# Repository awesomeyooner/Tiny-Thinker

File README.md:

# Tiny-Thinker
Barebones STM32 board I made to learn PCB design. I took inspiration from [this tutorial](https://www.youtube.com/watch?v=aVUqaB0IMh4) as well as many other videos from PhilsLab, Robert Feranec, and many more!

## Resources

Instead of putting them here, I've put all my notes in this [repo!](https://github.com/awesomeyooner/KiCAD-Library/blob/main/docs/notes/Getting-Started.md)

I hope they're useful!

## Features

This is a 4-Layer PCB centered around the **STM32F446RCT6** (same as STM32F446RET6 but with less flash) with the following stackup:

- **L1** - SIGNAL (with GND Pour)
- **L2** - GND Plane
- **L3** - GND Plane
- **L4** - 3.3V PWR Plane + SIGNAL

Implemented Features:
- USB C FS (Device only)
- 5V Power Multiplexing (5V from USB + 5V from external source)
- User-toggleable LED
- PWR LED
- 2 2x20 Header pins for stackable expansion boards

This board breaks out the following:
- SPI1 and SPI2 (with CS)
- I2C1
- CAN1 (No Transciever)
- SWDIO
- USB_FS
- 8 x TIM Channels
- 4 x ADC Channels
- 4 x GPIO

## Pictures

### Schematic

### Layout and Routing

### CAD

### Assembled Product

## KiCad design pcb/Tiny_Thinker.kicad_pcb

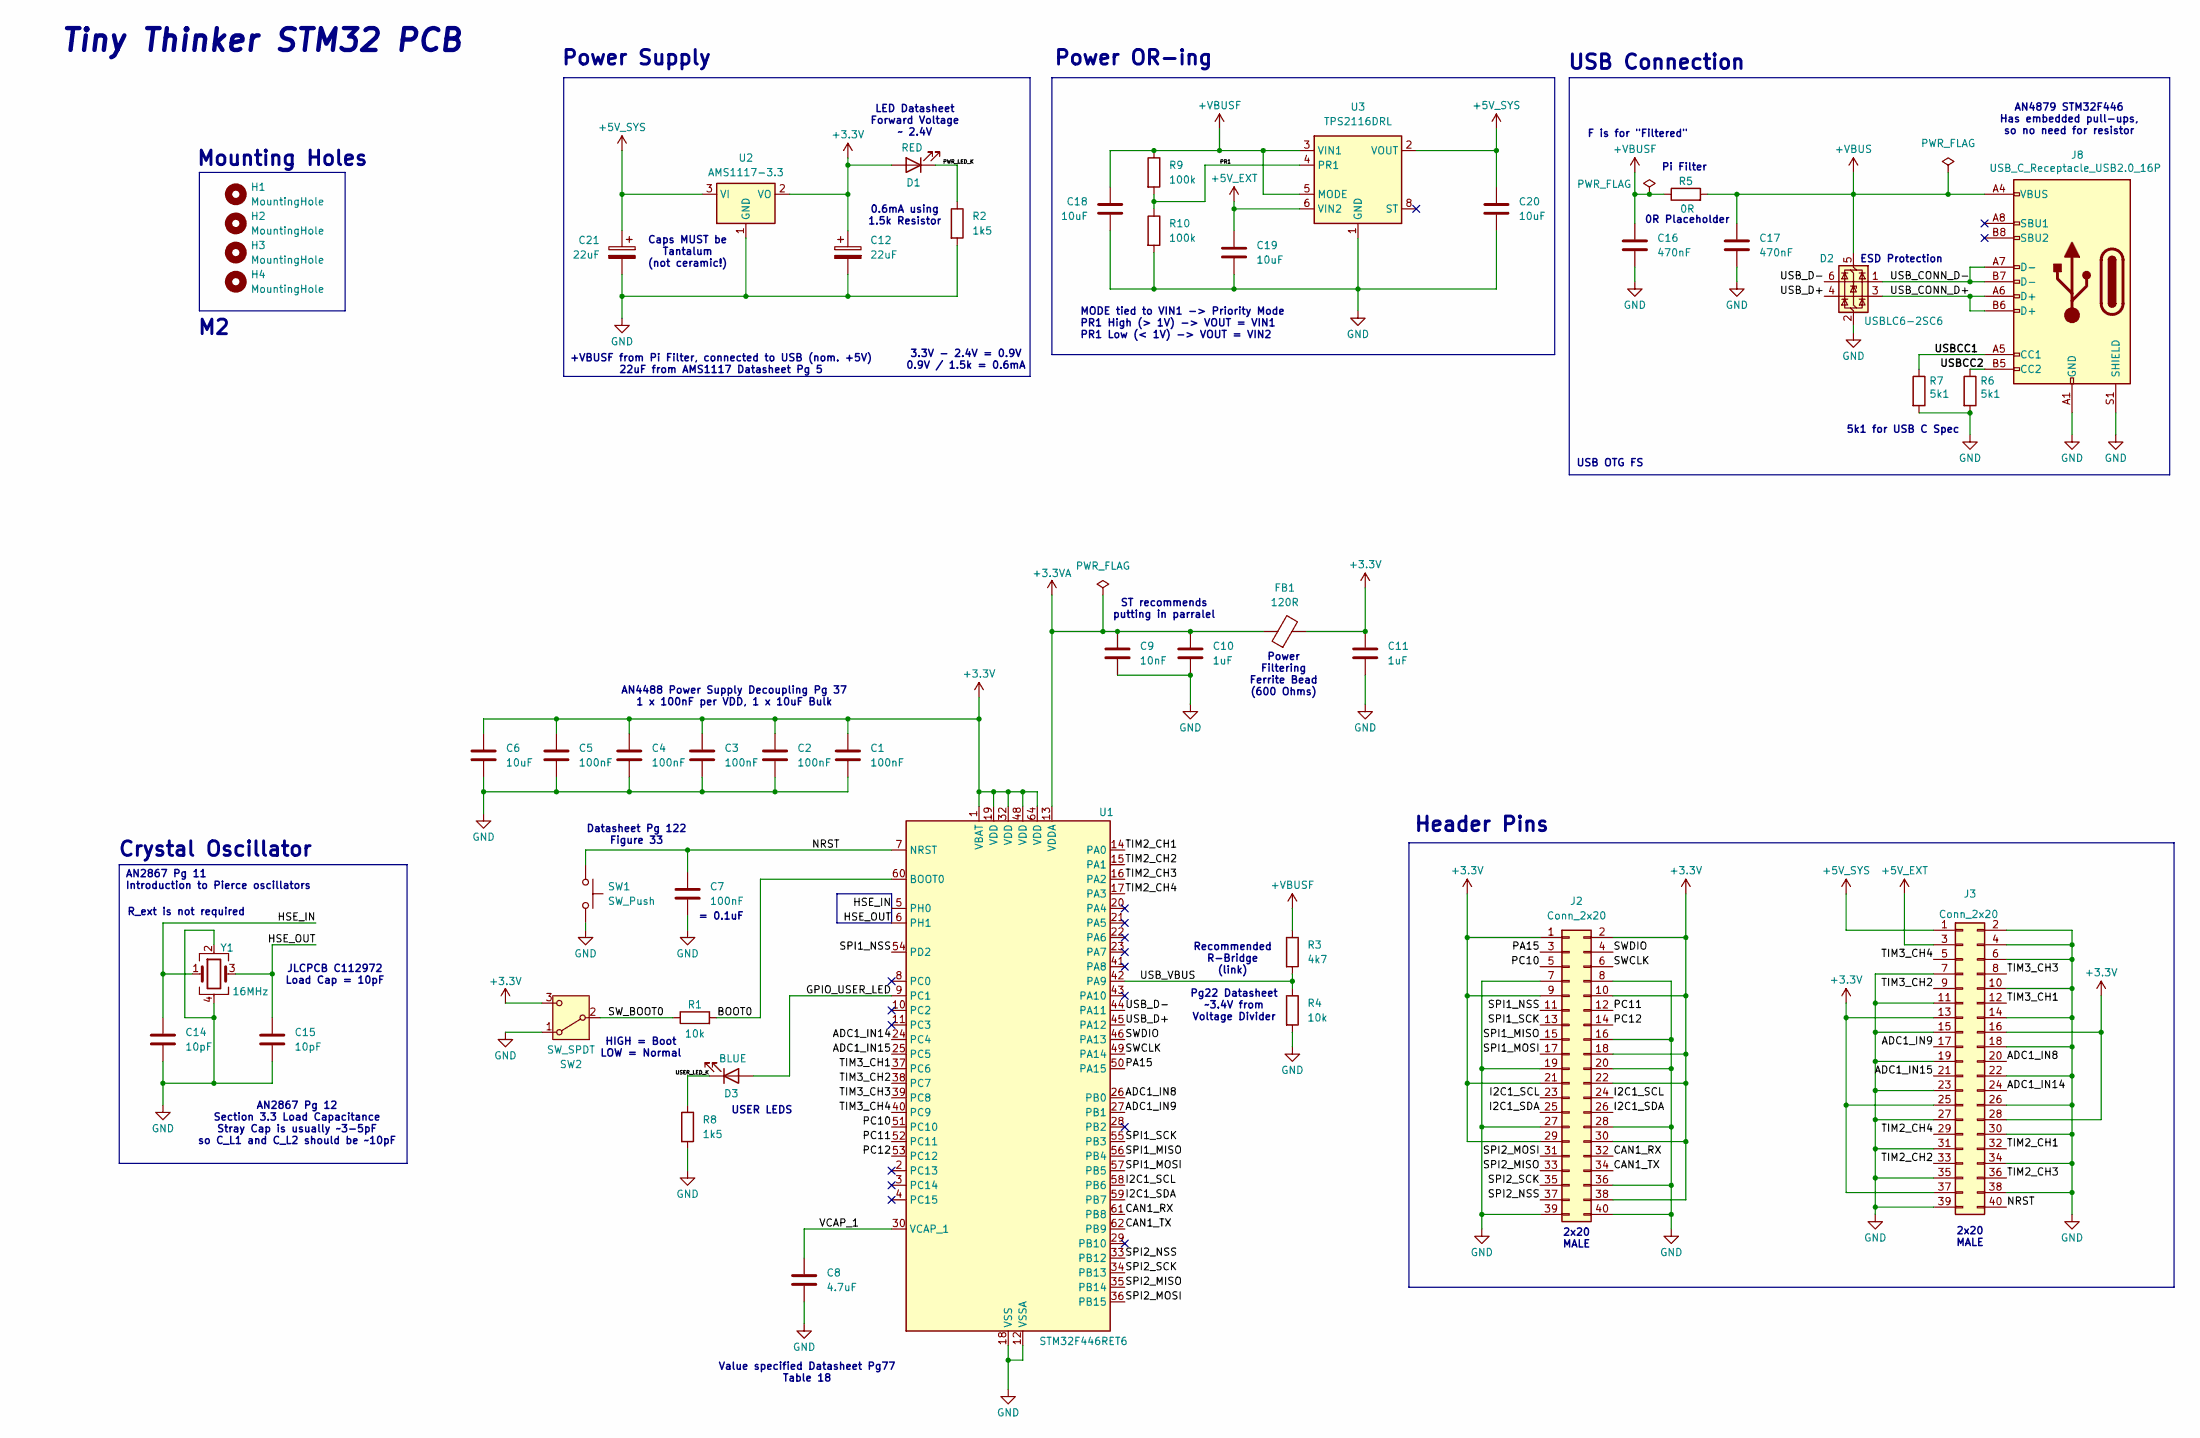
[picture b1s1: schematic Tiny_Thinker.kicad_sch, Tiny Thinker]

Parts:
C1, C2, C3, C4, C5, C7: 100nF; C_0402_1005Metric; JLCPCB Part # C1525
C6, C18, C19, C20: 10uF; C_0603_1608Metric; JLCPCB Part # C19702
C8: 4.7uF; C_0402_1005Metric; JLCPCB Part # C23733
C9: 10nF; C_0402_1005Metric; JLCPCB Part # C15195
C10, C11: 1uF; C_0402_1005Metric; JLCPCB Part # C52923
C12, C21: 22uF; CP_EIA-3216-18_Kemet-A; JLCPCB Part # C11366
C14, C15: 10pF; C_0402_1005Metric; JLCPCB Part # C32949
C16, C17: 470nF; C_0603_1608Metric; JLCPCB Part # C1623
D1: RED; LED_0603_1608Metric; JLCPCB Part # C2286
D2: USBLC6-2SC6; SOT-23-6; JLCPCB Part # C7519
D3: BLUE; LED_0603_1608Metric; JLCPCB Part # C2288
FB1: 120R; L_0603_1608Metric; JLCPCB Part # C1002
H1, H2, H3, H4: MountingHole; MountingHole_2.2mm_M2
J2, J3: Conn_2x20; PinHeader_2x20_P2.54mm_Vertical; JLCPCB Part # C50980
J8: USB_C_Receptacle_USB2.0_16P; USB_C_Receptacle_GCT_USB4105-xx-A_16P_TopMnt_Horizontal; JLCPCB Part # C2765186
R1, R4: 10k; R_0402_1005Metric; JLCPCB Part # C25744
R2, R8: 1k5; R_0402_1005Metric; JLCPCB Part # C25867
R3: 4k7; R_0402_1005Metric; JLCPCB Part # C25900
R5: 0R; R_0402_1005Metric; JLCPCB Part # C17168
R6, R7: 5k1; R_0402_1005Metric; JLCPCB Part # C25905
R9, R10: 100k; R_0603_1608Metric; JLCPCB Part # C25803
SW1: SW_Push; SW_SPST_TS-1088-xR020; JLCPCB Part # C720477
SW2: SW_SPDT; SW_SPDT_PCM12; JLCPCB Part # C431541
U1: STM32F446RET6; LQFP-64_10x10mm_P0.5mm; JLCPCB Part # C915971
U2: AMS1117-3.3; SOT-223-3_TabPin2; JLCPCB Part # C6186
U3: TPS2116DRL; SOT-583-8; JLCPCB Part # C3235557
Y1: 16MHz; Crystal_SMD_3225-4Pin_3.2x2.5mm; JLCPCB Part # C112972

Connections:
+3.3V: C1.1, C2.1, C3.1, C4.1, C5.1, C6.1, C11.1, C12.1, D1.2 (A), FB1.2, J2.1, J2.2, J2.9, J2.10, J2.18, J2.21, J2.22, J2.29, J2.30, J2.38, J3.13, J3.16, J3.25, J3.28, J3.37, SW2.3 (C), U1.1 (VBAT), U1.19 (VDD), U1.32 (VDD), U1.48 (VDD), U1.64 (VDD), U2.2 (VO)
+3.3VA: C9.1, C10.1, FB1.1, U1.13 (VDDA)
+5V_EXT: C19.1, J3.3, U3.6 (VIN2)
+5V_SYS: C20.1, C21.1, J3.1, U2.3 (VI), U3.2 (VOUT), U3.7 (VOUT)
+VBUS: C17.1, D2.5 (VBUS), J8.A4 (VBUS), J8.A9 (VBUS), J8.B4 (VBUS), J8.B9 (VBUS), R5.2
+VBUSF: C16.1, C18.1, R3.1, R5.1, R9.1, U3.3 (VIN1), U3.5 (MODE)
/ADC1_IN8: J3.20, U1.26 (PB0)
/ADC1_IN9: J3.17, U1.27 (PB1)
/ADC1_IN14: J3.24, U1.24 (PC4)
/ADC1_IN15: J3.21, U1.25 (PC5)
/BOOT0: R1.2, U1.60 (BOOT0)
/CAN1_RX: J2.32, U1.61 (PB8)
/CAN1_TX: J2.34, U1.62 (PB9)
/GPIO_USER_LED: D3.2 (A), U1.9 (PC1)
/HSE_IN: C14.1, U1.5 (PH0), Y1.1
/HSE_OUT: C15.1, U1.6 (PH1), Y1.3
/I2C1_SCL: J2.23, J2.24, U1.58 (PB6)
/I2C1_SDA: J2.25, J2.26, U1.59 (PB7)
/NRST: C7.1, J3.40, SW1.1, U1.7 (NRST)
/PA15: J2.3, U1.50 (PA15)
/PC10: J2.5, U1.51 (PC10)
/PC11: J2.12, U1.52 (PC11)
/PC12: J2.14, U1.53 (PC12)
/PR1: R9.2, R10.1, U3.4 (PR1)
/PWR_LED_K: D1.1 (K), R2.1
/SPI1_MISO: J2.15, U1.56 (PB4)
/SPI1_MOSI: J2.17, U1.57 (PB5)
/SPI1_NSS: J2.11, U1.54 (PD2)
/SPI1_SCK: J2.13, U1.55 (PB3)
/SPI2_MISO: J2.33, U1.35 (PB14)
/SPI2_MOSI: J2.31, U1.36 (PB15)
/SPI2_NSS: J2.37, U1.33 (PB12)
/SPI2_SCK: J2.35, U1.34 (PB13)
/SWCLK: J2.6, U1.49 (PA14)
/SWDIO: J2.4, U1.46 (PA13)
/SW_BOOT0: R1.1, SW2.2 (B)
/TIM2_CH1: J3.32, U1.14 (PA0)
/TIM2_CH2: J3.33, U1.15 (PA1)
/TIM2_CH3: J3.36, U1.16 (PA2)
/TIM2_CH4: J3.29, U1.17 (PA3)
/TIM3_CH1: J3.12, U1.37 (PC6)
/TIM3_CH2: J3.9, U1.38 (PC7)
/TIM3_CH3: J3.8, U1.39 (PC8)
/TIM3_CH4: J3.5, U1.40 (PC9)
/USBCC1: J8.A5 (CC1), R7.1
/USBCC2: J8.B5 (CC2), R6.1
/USB_CONN_D+: D2.3 (I/O2), J8.A6 (D+), J8.B6 (D+)
/USB_CONN_D-: D2.1 (I/O1), J8.A7 (D-), J8.B7 (D-)
/USB_D+: D2.4 (I/O2), U1.45 (PA12)
/USB_D-: D2.6 (I/O1), U1.44 (PA11)
/USB_VBUS: R3.2, R4.1, U1.42 (PA9)
/USER_LED_K: D3.1 (K), R8.1
/VCAP_1: C8.1, U1.30 (VCAP_1)
GND: C1.2, C2.2, C3.2, C4.2, C5.2, C6.2, C7.2, C8.2, C9.2, C10.2, C11.2, C12.2, C14.2, C15.2, C16.2, C17.2, C18.2, C19.2, C20.2, C21.2, D2.2 (GND), J2.7, J2.8, J2.16, J2.19, J2.20, J2.27, J2.28, J2.36, J2.39, J2.40, J3.2, J3.4, J3.6, J3.7, J3.10, J3.11, J3.14, J3.15, J3.18, J3.19, J3.22, J3.23, J3.26, J3.27, J3.30, J3.31, J3.34, J3.35, J3.38, J3.39, J8.A1 (GND), J8.A12 (GND), J8.B1 (GND), J8.B12 (GND), J8.S1 (SHIELD), R2.2, R4.2, R6.2, R7.2, R8.2, R10.2, SW1.2, SW2.1 (A), U1.12 (VSSA), U1.18 (VSS), U1.31 (VSS), U1.47 (VSS), U1.63 (VSS), U2.1 (GND), U3.1 (GND), Y1.2, Y1.4

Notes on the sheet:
Tiny Thinker STM32 PCB
Mounting Holes
Header Pins
+VBUSF from Pi Filter, connected to USB (nom. +5V) 22uF from AMS1117 Datasheet Pg 5
Pi Filter
Caps MUST be Tantalum (not ceramic!)
Crystal Oscillator
2x20 MALE
AN4488 Power Supply Decoupling Pg 37 1 x 100nF per VDD, 1 x 10uF Bulk
0R Placeholder
Power OR-ing
HIGH = Boot LOW = Normal
ESD Protection
F is for "Filtered"
USB Connection
MODE tied to VIN1 -> Priority Mode PR1 High (> 1V) -> VOUT = VIN1 PR1 Low (< 1V) -> VOUT = VIN2
Power Filtering Ferrite Bead (600 Ohms)
AN4879 STM32F446 Has embedded pull-ups, so no need for resistor
USER LEDS
Value specified Datasheet Pg77 Table 18
= 0.1uF
3.3V - 2.4V = 0.9V 0.9V / 1.5k = 0.6mA
JLCPCB C112972 Load Cap = 10pF
USB OTG FS
AN2867 Pg 11 Introduction to Pierce oscillators
LED Datasheet Forward Voltage ~ 2.4V
0.6mA using 1.5k Resistor
AN2867 Pg 12 Section 3.3 Load Capacitance Stray Cap is usually ~3-5pF so C_L1 and C_L2 should be ~10pF
ST recommends putting in parralel
R_ext is not required
5k1 for USB C Spec
Pg22 Datasheet ~3.4V from Voltage Divider
Power Supply
Recommended R-Bridge (link)
Datasheet Pg 122 Figure 33

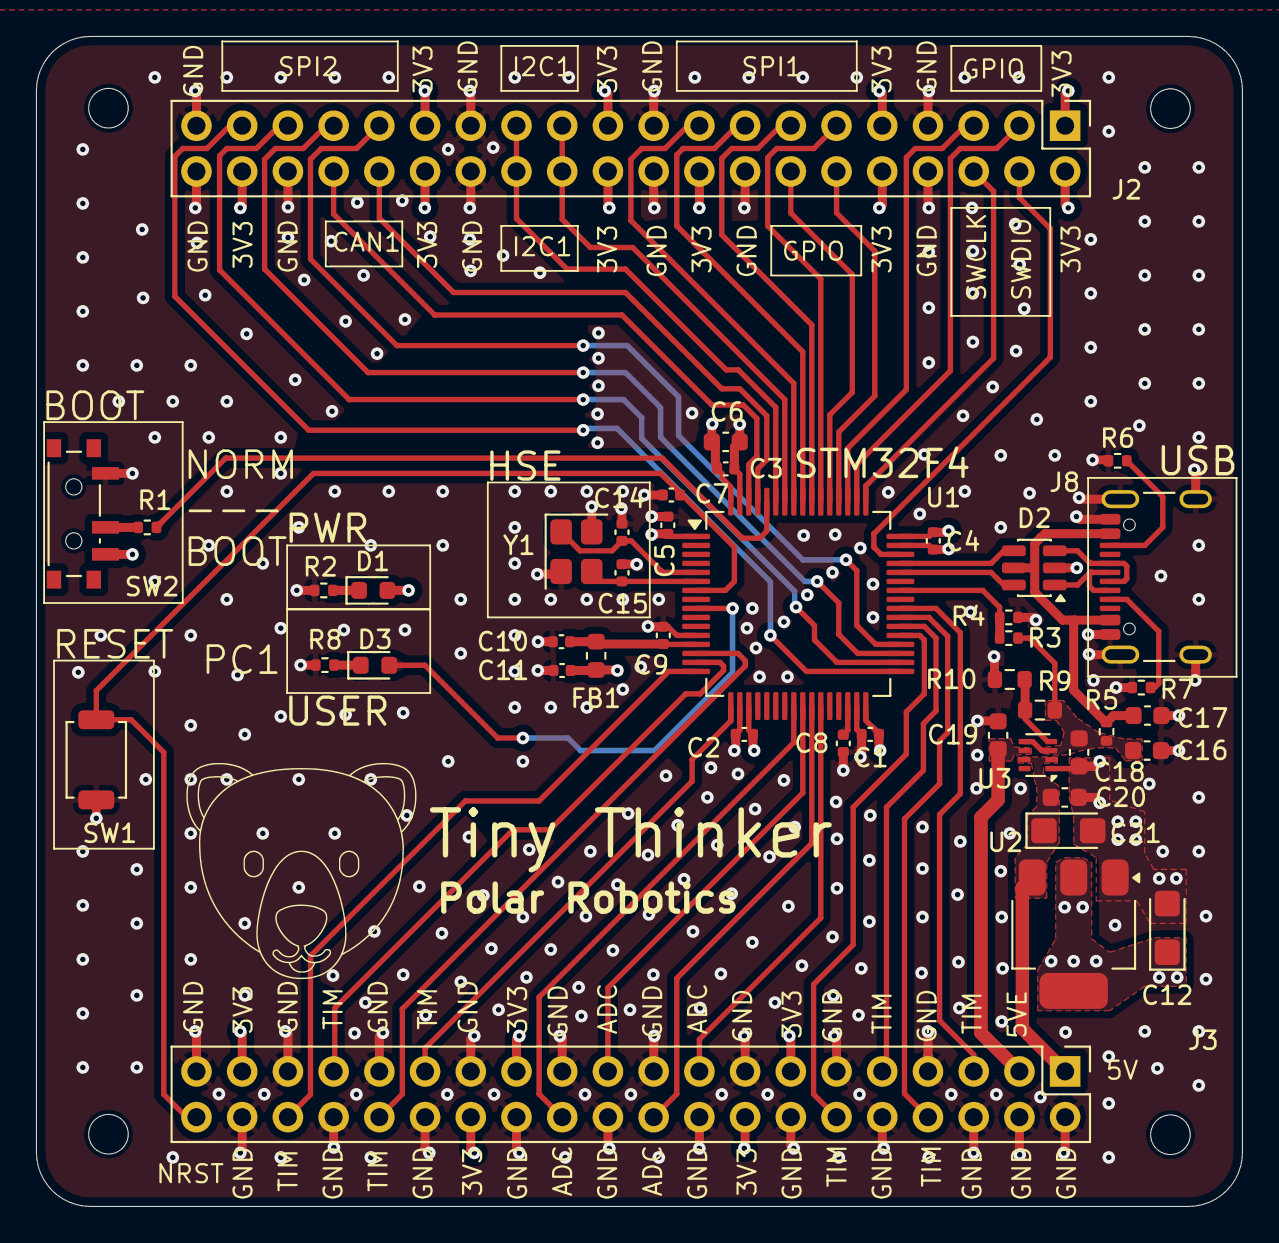
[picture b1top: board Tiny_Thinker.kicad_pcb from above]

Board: 4 copper layers, 67.0 x 65.0 mm, 47 parts (0 on the bottom side), 54 nets.

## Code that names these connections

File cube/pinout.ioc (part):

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Mcu.Name=STM32F446R(C-E)Tx
Mcu.Package=LQFP64
Mcu.UserName=STM32F446RETx
PA0-WKUP.Signal=S_TIM2_CH1_ETR
PA1.Signal=S_TIM2_CH2
PA11.Mode=Device_Only
PA11.Signal=USB_OTG_FS_DM
PA12.Mode=Device_Only
PA12.Signal=USB_OTG_FS_DP
PA13.Mode=Serial_Wire
PA13.Signal=SYS_JTMS-SWDIO
PA14.Mode=Serial_Wire
PA14.Signal=SYS_JTCK-SWCLK
PA2.Signal=S_TIM2_CH3
PA3.Signal=S_TIM2_CH4
PA9.Mode=Activate_VBUS
PA9.Signal=USB_OTG_FS_VBUS
PB0.Signal=ADCx_IN8
PB1.Signal=ADCx_IN9
PB12.Signal=SPI2_NSS
PB13.Mode=Full_Duplex_Master
PB13.Signal=SPI2_SCK
PB14.Mode=Full_Duplex_Master
PB14.Signal=SPI2_MISO
PB15.Mode=Full_Duplex_Master
PB15.Signal=SPI2_MOSI
PB3.Mode=Full_Duplex_Master
PB3.Signal=SPI1_SCK
PB4.Mode=Full_Duplex_Master
PB4.Signal=SPI1_MISO
PB5.Mode=Full_Duplex_Master
PB5.Signal=SPI1_MOSI
PB6.Mode=I2C
PB6.Signal=I2C1_SCL
PB7.Mode=I2C
PB7.Signal=I2C1_SDA
PB8.Mode=CAN_Activate
PB8.Signal=CAN1_RX
PB9.Mode=CAN_Activate
PB9.Signal=CAN1_TX
PC4.Signal=ADCx_IN14
PC5.Signal=ADCx_IN15
PC6.Signal=S_TIM3_CH1
PC7.Signal=S_TIM3_CH2
PC8.Signal=S_TIM3_CH3
PC9.Signal=S_TIM3_CH4
PD2.Signal=GPIO_Output
PH0-OSC_IN.Mode=HSE-External-Oscillator
PH0-OSC_IN.Signal=RCC_OSC_IN
PH1-OSC_OUT.Mode=HSE-External-Oscillator
PH1-OSC_OUT.Signal=RCC_OSC_OUT
RCC.HSE_VALUE=16000000
RCC.SYSCLKFreq_VALUE=180000000
RCC.SYSCLKSource=RCC_SYSCLKSOURCE_PLLRCLK
board=custom

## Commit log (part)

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2025-09-25 added initial project
2025-09-25 removed unused cpl
2025-09-27 reorganized project structure
2025-09-27 added pinout.ioc
2025-09-28 added resources to readme
2025-10-04 added 40pin (WIP)
2025-10-05 added extra 100nf cap
2025-10-13 I honestly forgot what I did
2025-10-14 i dont even know
2026-01-07 added redesign project so I can use the old one as reference
2026-01-07 switched names
2026-01-08 changed pinout
2026-01-08 added more comments are made the schematic neater
2026-01-08 added USB C with ESD Protection
2026-01-08 more comments
2026-01-08 Assigned footprints
2026-01-08 gave colors to all netclasses
2026-01-08 Added JLCPCB capabilities
2026-01-08 before I start editting the pcb
2026-01-08 added colors
2026-01-08 checkpoint
2026-01-08 i forgot to add this one
2026-01-08 deleted everyting
2026-01-08 renamed the capacitors to be in order
2026-01-08 unlock
2026-01-09 rough layout done
2026-01-23 routed traces, changed 2x16 to 2x20, defined the dimensions
2026-01-23 I forgot to save. The previous message is what this commit is
2026-01-23 im not sure what I did
2026-01-24 named USB connectors
    idk why they keep on resetting
2026-01-24 routed peripherals
2026-01-24 i forgot to save again
2026-01-24 added misc pins
2026-01-24 added ground pour to L1
2026-01-24 finished adding vias to header pins (not stitching)
2026-01-24 started adding stitching vias
2026-01-24 added logo
2026-01-24 updated bom / added JLC part #
2026-01-24 refreshed bom
2026-01-24 updated ioc
2026-01-28 Revised JLCPCB capabilities
2026-01-28 cleaned up routing of USB data lines
2026-01-28 Added more comments
2026-01-30 unlocked
2026-01-30 updateed ioc
2026-01-30 added code generation
2026-01-31 removed cube code
2026-01-31 readded cubemx files
2026-01-31 renamed pinout folder to cube (for stm32cubemx)
2026-02-06 renamed USB C net labels
2026-02-06 changed header routing to be more spaced out
2026-02-06 Added user led
2026-02-06 cleaned up routing
2026-02-06 removed stitching vias
2026-02-06 changed dimensions to be whole numbers
2026-02-06 added and routed TPS2116 Power OR-ing IC
2026-02-06 added copper pour for VBUSF
2026-02-06 broke out +5V external supply for expandability
2026-02-06 DRC cehck
2026-02-07 unlocked project
2026-02-12 changed 10k Ohm resistor JLCPCB part and removed fiducial markers (jlc does it for you)
2026-02-12 rearranged silkscreen
2026-02-17 added stitching vias and cleaned up silkscreen
2026-02-17 added more stitching vias
2026-02-17 removed DNP from BOM
2026-02-20 moved NRST 100nF capacitor closer to pin
2026-02-20 unlocked files
2026-02-21 renamed header connectors for BOM and connected NRST to a pin
2026-02-21 put knockout text on NRST pin
2026-02-22 Added silkscreen for USER LED
2026-02-22 updated gerbers
2026-02-25 added more comments to schematic
2026-02-25 changed AMS caps to tantalum per spec
2026-02-25 comments on TPS2116
2026-02-25 added manufacturing files
2026-02-25 minor ground plane edits
2026-02-25 regenerated manufacturing files
2026-02-26 updated manufacturing files
2026-02-26 minor changes to GND plane
    I hate being paranoid
2026-03-07 added blink firmware
2026-04-05 Added STEP Files
